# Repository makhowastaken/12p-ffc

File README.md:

# 12p-ffc
A 12 pin FFC breakout board fpr 12 pin 0.5mm pitch FFC cables

You need these PCBs (flex board preferred but the thinner the better otherwise), some 12 pin 0.5mm pitch flat flex cables, and some 12 pin 0.5mm pitch connectors. 

NOTE: It is important that the cable itself terminates on opposite sides OR that you use a top connect connector or a bottom connect connector otherwise the pin numbers will NOT match on either side (12 ≠ 12, 12 = 1)

Parts I used:
* [0.5mm pitch flat flex cable (same side termination)](https://www.aliexpress.com/item/32970287189.html)
* [0.5mm pitch flat flex connector (bottom contact)](https://www.aliexpress.com/item/32956902542.html)
* [0.5mm pitch flat flex connector (top contact)](https://www.aliexpress.com/item/32958184639.html)
* [the PCBs listed in this repo](https://oshpark.com/shared_projects/38voxUwq)

Yes, I used all four of these. One board has the top connect connectors and the other has the bottom connect connecotrs. Please see [this video]() for more info and install, otherwise this project should be relatively self explanatory. 

#Board Renders

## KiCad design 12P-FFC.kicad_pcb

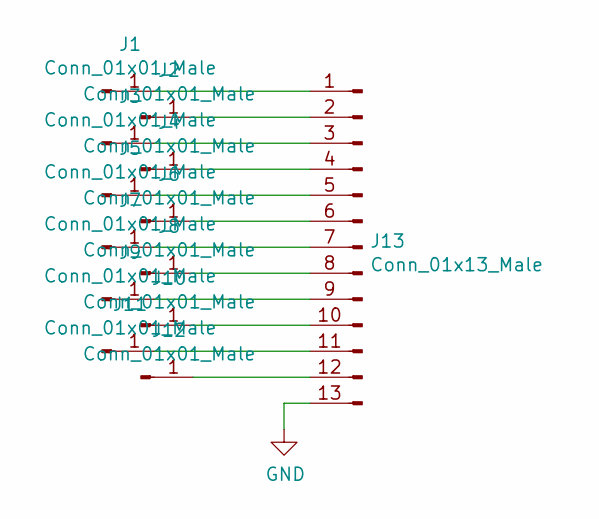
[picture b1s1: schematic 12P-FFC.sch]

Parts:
J1, J2, J3, J4, J5, J6, J7, J8, J9, J10, J11, J12: Conn_01x01_Male; TestPoint_Pad_D1.5mm
J13: Conn_01x13_Male; TE_1-1734839-2_1x12-1MP_P0.5mm_Horizontal

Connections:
GND: J13.13
unnamed: J1.1, J13.1
unnamed: J10.1, J13.10
unnamed: J11.1, J13.11
unnamed: J12.1, J13.12
unnamed: J2.1, J13.2
unnamed: J3.1, J13.3
unnamed: J4.1, J13.4
unnamed: J5.1, J13.5
unnamed: J6.1, J13.6
unnamed: J7.1, J13.7
unnamed: J8.1, J13.8
unnamed: J9.1, J13.9

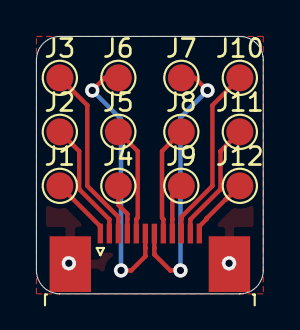
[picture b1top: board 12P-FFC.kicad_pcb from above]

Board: 2 copper layers, 12.6 x 14.3 mm, 13 parts (0 on the bottom side), 12 nets.
